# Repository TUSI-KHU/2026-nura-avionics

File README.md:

# NURA Standard Avionics RTOS

Zephyr RTOS 기반 NURA 에비오닉스 펌웨어입니다. 비행 판단은 하드웨어와 분리된
Domain에 두고, 보드·센서·recovery 출력은 PSP(Platform Support Package) adapter로
교체합니다. 모든 task는 bounded Software Bus로 통신하며, 실행 순서와 FSM 전이는
TraceMap으로 재구성합니다.

현재 상태: `native_sim` 및 `teensy41` cross-build 검증 완료. 실제 Teensy 4.1 및
센서 보드가 없는 상태에서 작성되었으므로 **하드웨어 검증 전 비행 금지**입니다.

## Layout

```text
modules/contracts/       Typed message contracts
modules/domain/flight/   Pure FSM policy and state applications
modules/core/            Software Bus, Executive, TraceMap
modules/apps/            Input, coordination, recovery, recorder apps
modules/platform/        PSP ports and host fakes
firmware/zephyr/         Zephyr board integration and adapters
test/zephyr_port/        Host replay and fault-guard tests
tools/host_sim/          Deterministic flight simulator
tools/app_catalog/       Generated schedule and state-app matrix
documents/               Architecture, safety policy, TraceMap usage
avionics_project/        Current KiCad hardware design
```

## Build And Validate

```bash
scripts/setup-zephyr.sh
scripts/validate-migration.sh
scripts/build-zephyr.sh native_sim
scripts/build-zephyr.sh teensy41
```

`scripts/validate-migration.sh` builds the host tests, produces a complete
TraceMap flight trace, and runs Zephyr builds when the local Zephyr workspace
is installed.

현재 thread schedule과 FSM별 application은
[`documents/runtime_app_catalog.generated.md`](documents/runtime_app_catalog.generated.md)에서
확인할 수 있으며 검증 시 App Catalog와 자동 비교됩니다.

## Safety Boundary

- `modules/domain/flight/` must not include Zephyr, MCU, sensor driver, or GPIO
  headers.
- `FlightPolicy::kPyroFireDurationMs` is **1000 ms**, the current mission
  policy. Hardware output qualification remains required before flight.
- Recovery ON requests are accepted only through the Coordinator and guarded
  Recovery application; command parsing and debug paths cannot drive GPIO.

Detailed operational guidance is in [documents/README.md](documents/README.md).

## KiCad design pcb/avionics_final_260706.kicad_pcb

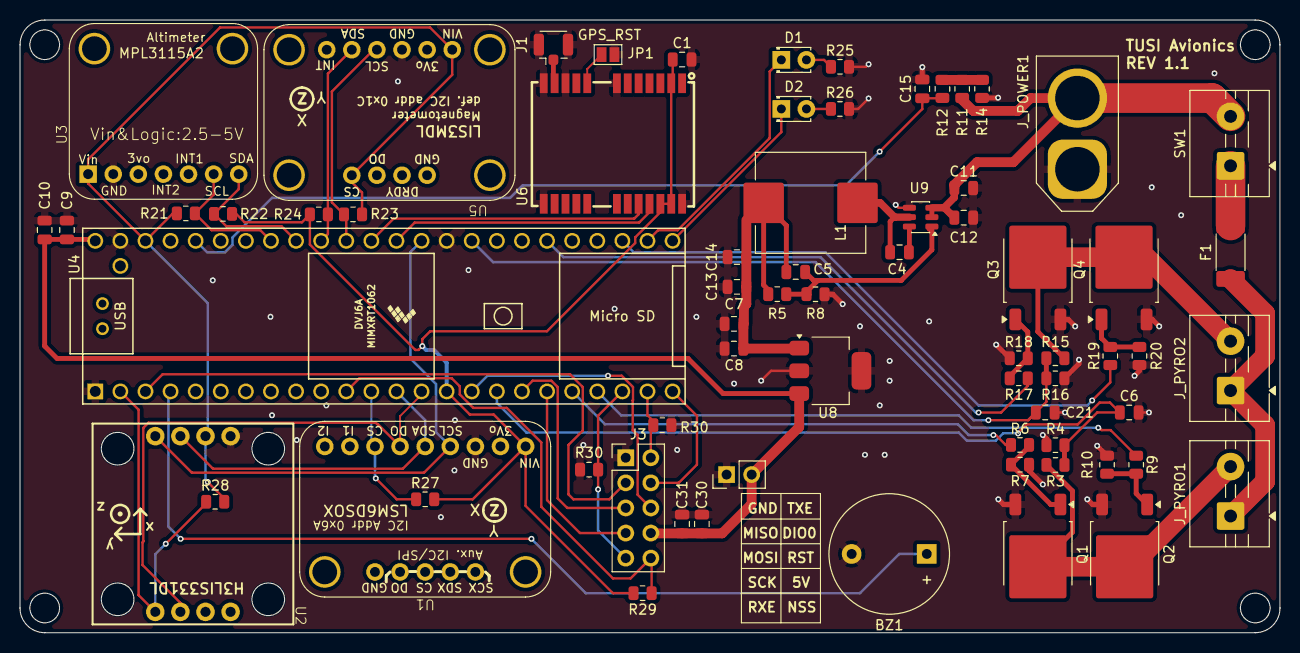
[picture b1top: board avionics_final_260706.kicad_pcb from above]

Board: 2 copper layers, 127.5 x 62.0 mm, 69 parts (0 on the bottom side), 49 nets.

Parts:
BZ1: Buzzer; Buzzer_12x9.5RM7.6
C1: 1u; C_0805_2012Metric
C4, C6, C7, C9, C11, C15, C21, C30: 100n; C_0805_2012Metric
C5: 100p; C_0805_2012Metric
C8, C31: 10u; C_0805_2012Metric
C10, C12, C13, C14: 22u; C_0805_2012Metric
D1, D2: LED; LED_D1.8mm_W3.3mm_H2.4mm
F1: 5A; Fuse_2410_6127Metric
J1: U.FL-R-SMT-1(10); U.FL_Hirose_U.FL-R-SMT-1_Vertical
J3: Conn_LoRA; PinHeader_2x05_P2.54mm_Vertical
JP1: GPS_RST; SolderJumper-2_P1.3mm_Open_Pad1.0x1.5mm
J_POWER1: XT60; AMASS_XT60-F_1x02_P7.20mm_Vertical
J_PYRO1, J_PYRO2: IGNITER_5R6; TerminalBlock_MaiXu_MX126-5.0-02P_1x02_P5.00mm
L1: 10uH; L_Changjiang_FXL1050
Q1, Q2, Q3, Q4: IRLR8726; TO-252-2
R3, R15: 330k; R_0805_2012Metric
R4, R16: 68k; R_0805_2012Metric
R5: 180k; R_0805_2012Metric
R6, R9, R17, R19: 100; R_0805_2012Metric
R7, R10, R18, R20, R30, R30#2: 100k; R_0805_2012Metric
R8: 30k; R_0805_2012Metric
R11: 150k; R_0805_2012Metric
R12: 1k; R_0805_2012Metric
R14: 33k; R_0805_2012Metric
R21, R22, R23, R24, R27, R28, R29: 4.7k; R_0805_2012Metric
R25, R26: 220; R_0805_2012Metric
SW1: ARM; TerminalBlock_MaiXu_MX126-5.0-02P_1x02_P5.00mm
U1: Adafruit_LSM6DSO32; LSM6DSOX
U2: Sparkfun_H3LIS331DL
U3: Adafruit_MPC3315A2
U4: Teensy4.1; Teensy41
U5: LIS3MDL; Adafruit_LIS3MDL
U6: NEO-M9N-00B; GPSM-SMD_24P-L16.0-W12.2-P1.10-BL
U8: MCP1826S-5002; SOT-223-3_TabPin2
U9: AP63200WU-7; TSOT-23-6
pinheader: PinHeader_1x02_P2.54mm_Vertical

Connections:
+5V: C9.1, C10.1, C30.1, C31.1, J3.8, U4.48 (VIN), U8.3 (VO), pinheader.2
+5V6: C5.1, C5.2, C7.1, C8.1, C13.1, C14.1, L1.2, R5.1, R5.2, R8.1, U8.1 (VI), U9.1 (FB)
+BATT: C11.1, C12.1, J_POWER1.2, R11.1, SW1.2 (B), U9.2 (EN), U9.3 (IN)
/+3V3: C1.1, R21.1, R22.2, R23.1, R24.2, R27.2, R28.2, R29.2, U1.1 (VIN), U2.2 (3.3v), U3.1 (Vin), U4.15 (3V3), U4.46 (3V3), U5.1 (VIN), U5.10 (CS), U6.2 (D_SEL), U6.22 (V_BCKP), U6.23 (VCC)
/+BATT_ARMED: F1.2, J_PYRO1.1, J_PYRO2.1
/ADC_PYRO1_SENSE: C6.1, R3.1, R4.2, U4.17 (25_A11_RX6_SDA2)
/ADC_PYRO2_SENSE: C21.1, R15.1, R16.2, U4.33 (41_A17)
/BUZZER_PIN: BZ1.1 (+), U4.4 (2_OUT2)
/CS_IMU_HIGHG: R28.1, U2.8 (CS), U4.2 (0_RX1_CRX2_CS1)
/CS_IMU_LOWG: R27.1, U1.7 (CS), U4.12 (10_CS_MQSR)
/GPS_ANT: J1.1 (In), U6.11 (RF_IN)
/GPS_RX: U4.37 (15_A1_RX3_SPDIF_IN), U6.20 (TXD/SPI-MISO)
/GPS_TX: U4.36 (14_A0_TX3_SPDIF_OUT), U6.21 (RXD/SPI-MOSI)
/I2C0_SCL: R21.2, U3.6 (SCL), U4.41 (19_A5_SCL)
/I2C0_SDA: R22.1, U3.7 (SDA), U4.40 (18_A4_SDA)
/I2C1_SCL: R23.2, U4.38 (16_A2_RX4_SCL1), U5.4 (SCL)
/I2C1_SDA: R24.1, U4.39 (17_A3_TX4_SDA1), U5.5 (SDA)
/LED_GPIO1: D1.1 (K), U4.26 (34_RX8)
/LED_GPIO2: D2.1 (K), U4.25 (33_MCLK2)
/LORA_BUSY: J3.2, R30.1, U4.23 (31_CTX3)
/LORA_DIO1: J3.4, U4.24 (32_OUT1B)
/LORA_NSS: J3.10, R29.1, U4.11 (9_OUT1C)
/LORA_RST: J3.6, U4.16 (24_A10_TX6_SCL2)
/LORA_RXE: J3.9, R30#2.1, U4.22 (30_CRX3)
/PYRO1_2: J_PYRO1.2, Q1.2 (D), Q2.2 (D), R3.2
/PYRO1_GPIO1: R6.1, U4.20 (28_RX7)
/PYRO1_GPIO2: R9.1, U4.21 (29_TX7)
/PYRO2_2: J_PYRO2.2, Q3.2 (D), Q4.2 (D), R15.2
/PYRO2_GPIO1: R17.1, U4.30 (38_CS1_IN1)
/PYRO2_GPIO2: R19.1, U4.27 (35_TX8)
/SPI0_MISO: U1.6 (DO), U2.7 (SA0), U4.14 (12_MISO_MQSL)
/SPI0_MOSI: U1.5 (SDA), U2.3 (SDA), U4.13 (11_MOSI_CTX1)
/SPI0_SCK: U1.4 (SCL), U2.4 (SCL), U4.35 (13_SCK_LED)
/SPI1_MISO: J3.3, U4.3 (1_TX1_CTX2_MISO1)
/SPI1_MOSI: J3.5, U4.18 (26_A12_MOSI1)
/SPI1_SCK: J3.7, U4.19 (27_A13_SCK1)
/VBAT_MON: C15.1, R12.2, U4.44 (22_A8_CTX1)
GND: BZ1.2 (-), C1.2, C6.2, C7.2, C8.2, C9.2, C10.2, C11.2, C12.2, C13.2, C14.2, C15.2, C21.2, C30.2, C31.2, J1.2 (Ext), J3.1, JP1.2 (B), J_POWER1.1, Q1.3 (S), Q2.3 (S), Q3.3 (S), Q4.3 (S), R4.1, R7.1, R8.2, R10.1, R14.1, R16.1, R18.1, R20.1, R25.2, R26.2, R30.2, R30#2.2, U1.3 (GND), U2.1 (GND), U3.2 (GND), U4.1 (GND), U4.34 (GND), U4.47 (GND), U5.3 (GND), U6.7 (V_USB), U6.10 (GND), U6.12 (GND), U6.13 (GND), U6.24 (GND), U8.2 (GND), U9.4 (GND), pinheader.1
unnamed: D1.2 (A), R25.1
unnamed: D2.2 (A), R26.1
unnamed: JP1.1 (A), U6.8 (RESET_N)
unnamed: Q1.1 (G), R6.2, R7.2
unnamed: Q2.1 (G), R9.2, R10.2
unnamed: Q3.1 (G), R17.2, R18.2
unnamed: Q4.1 (G), R19.2, R20.2
unnamed: R11.2, R12.1, R14.2
unnamed: F1.1, SW1.1 (A)
unnamed: C4.2, U9.6 (BST)
unnamed: C4.1, L1.1, U9.5 (SW)

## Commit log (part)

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2026-04-08 Reformat codes and switch environment to nano
2026-04-09 Purge legacy sensor stack for architecture reset
2026-04-09 feat: add scheduler and FSM task structure
2026-04-09 feat: ringbuffer based logger and serial interface
2026-04-09 feat: add MPU6050 HAL and IMU sensor task
2026-04-09 feat: improve runtime health handling for imu, logger, and scheduler
2026-04-09 wip: added failure detection and recovery watchdog task
2026-04-09 fix: removed unnecessary archive file
2026-04-14 feat: recoverabletask and watchdogtask impl
2026-04-20 Add: Comments
2026-04-20 refactor: flight controller app into modular tasks and states
2026-05-05 port on teensy4.1
2026-05-05 add project architecture
2026-05-05 add project architecture image
2026-05-11 hello I'm seohyein
2026-05-12 add sensor calibration logic on hal && calibration demand on sensors.md
2026-05-13 add uniform sensor test (not included proj. target)
2026-05-13 lora unit test complete. (근데 사실 패킷구조 정의 이런건 하나도 안함... ㅎㅎ) 그냥 잘 돌아가는데까지 어마무시한 시간이 걸렸습니다. 이제 전압 플로팅같은건 없이 안정화는 되었으니깐, 패킷구조 정의할거구요, 나머지 로직도 짤거에요. 참고로 그냥 LORA.h 기본파일 쓰면 안되고 mode bit 수정해야 잘되네요?? 하하 샤갈
2026-05-14 add AGENTS.md document 폴더 만들고 센서랑 요구사항들도 추가했어
2026-05-14 sensor_test 추가했어요. HAL 만들기 전에 센서 테스트한 코드는 여기다가 임시로 올리시면 됩니다.
2026-05-14 add all_set and all_get func
2026-05-15 Add SPI H3LIS331DL high-g IMU module
2026-05-16 gnss
2026-05-17 09fcc77까지 fast-forward, lora update
2026-05-17 Add LSM6DSO32 low-g IMU SPI integration
2026-05-17 Add MAG task and state
2026-05-18 readme(kr)
2026-05-18 0518 - 모든 센서 테스트 및 HAL, state, fc 통합 완료
2026-05-21 비행 로직넣을때 (의도하지않은)AI에 의한 추가방지 지침 추가, 로직 추가 시 문서화 필수조건 설
2026-05-21 Add Apache 2.0 license
2026-05-23 상태머신 로직추가 및 테스트 로직 업그레이
2026-05-23 소스코드 내 모든 상수 단일 파일로 분
2026-05-23 Grounding status 수정
2026-05-24 baro fault 감지 및 실시 드로그 로직(IMU기반) 추가
2026-05-25 IMU fault 로직 추가
2026-05-25 Lora
2026-05-28 add logger logic
2026-05-29 Fix LoRa pair test tooling
2026-05-29 Fix macOS Teensy bootloader upload
2026-05-29 test1
2026-05-29 flash 로직추가 (미완)
2026-05-30 로거 완성 + 기말고사전까지 쉬다올게요
2026-06-22 실기판기반 핀맵수정 & 로거로직추가 & 파이로 로직추가 & 버저 구현 추가 & 배터리 전압 체킹 및 변환 로직추가 & pcb lora sx1276으로 변
2026-06-22 통신을 위한 시도
2026-06-22 lora_fix
2026-06-23 fixed
2026-06-23 blocking I/O 전부 non-blocking으로 수정, 로라 안정성 체크
2026-06-23 init fail 로직수정
2026-06-25 레거시 hal제거, 파이로2번 간섭으로 임시 비활성화,pcb업로
2026-06-26 시험발사용 프로젝트 fork 추가
2026-06-26 만능기판용 땜빵코드 추가
